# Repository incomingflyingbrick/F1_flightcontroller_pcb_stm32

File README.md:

# F1_flightcontroller_pcb_stm32

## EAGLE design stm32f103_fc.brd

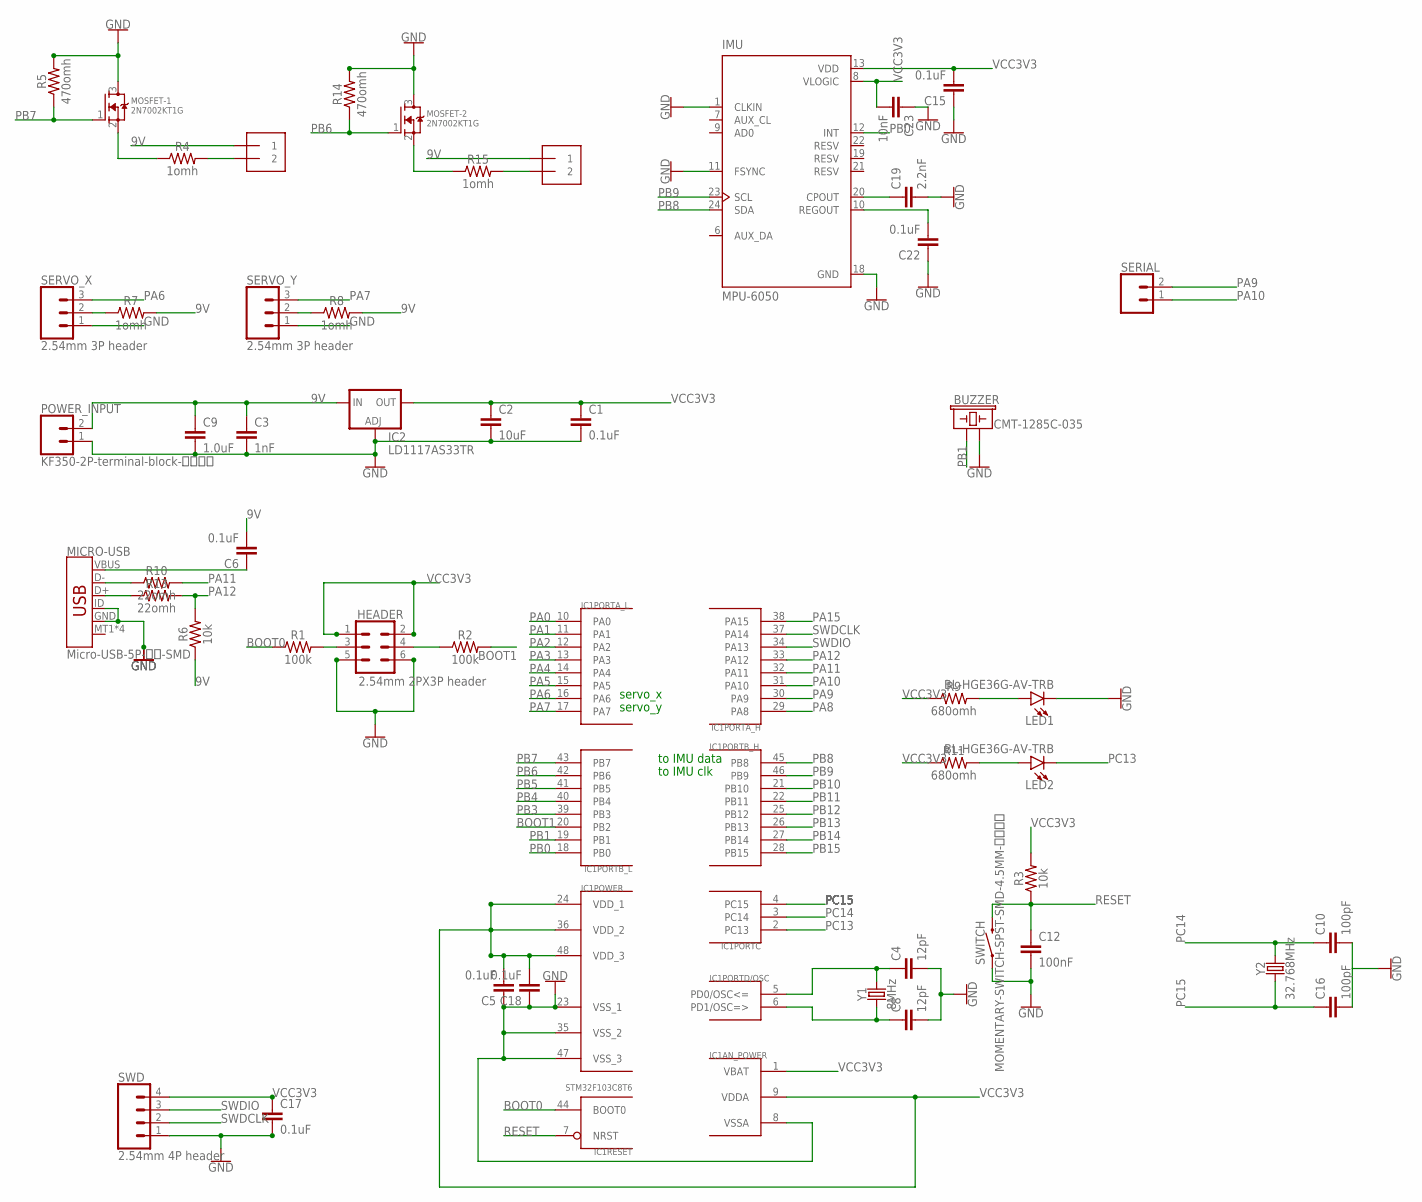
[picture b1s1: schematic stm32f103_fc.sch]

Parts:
BUZZER: CMT-1285C-035; BUZZER-12MM
C1, C6, C17: 0.1uF; 0603
C2: 10uF; 0603
C3: 1nF; 0603
C4, C8: 12pF; 0603
C5, C15, C18, C22: 0.1uF; 0402
C9: 1.0uF; 0603
C10, C16: 100pF; 0603
C12: 100nF; 0603
C19: 2.2nF; 0603
C23: 10nF; 0603
HEADER: 2.54mm 2PX3P header; 2X3-NS
IC1: STM32F103C8T6; TQFP48
IC2: LD1117AS33TR; SOT223
IMU: MPU-6050; QFN50P400X400X95-24N
LED1, LED2: BL-HGE36G-AV-TRB; LED-0603
MICRO-USB: Micro-USB-5P-无柱-SMD; USB-MICROB
MOSFET-1, MOSFET-2: 2N7002KT1G; SOT23
POWER_INPUT: KF350-2P-terminal-block-接线端子; SCREWTERMINAL-3.5MM-2
PY1, PY2: 1X2-3.5MM KF350 terminal block; 1X2-3.5MM
R1, R2: 100k; 0603
R3, R6: 10k; 0603
R4, R7, R8, R15: 1omh; 0603
R5, R14: 470omh; 0603
R9, R11: 680omh; 0603
R10, R13: 22omh; 0603
SERIAL: CONN_02; 1X02
SERVO_X: 2.54mm 3P header; 1X03
SERVO_Y: 2.54mm 3P header; 1X03
SWD: 2.54mm 4P header; 1X04
SWITCH: MOMENTARY-SWITCH-SPST-SMD-4.5MM-轻触开关; TACTILE_SWITCH_SMD_6.0X3.5MM
Y1: 8MHz; HC49US
Y2: 32.768MHz; HC49US

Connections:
9V: C3.1, C6.2, C9.1, IC2.3 (IN), POWER_INPUT.2, PY1.1, PY2.1, R6.1, R7.2, R8.2
BOOT0: IC1.44 (BOOT0), R1.1
BOOT1: IC1.20 (PB2), R2.2
GND: BUZZER.- (2), C1.2, C2.2, C3.2, C4.2, C5.1, C8.2, C9.2, C10.2, C12.2, C15.1, C16.2, C17.2, C18.1, C19.2, C22.1, C23.1, HEADER.5, HEADER.6, IC1.8 (VSSA), IC1.23 (VSS_1), IC1.35 (VSS_2), IC1.47 (VSS_3), IC2.1 (ADJ), IMU.1 (CLKIN), IMU.11 (FSYNC), IMU.18 (GND), LED1.C, MICRO-USB.GND, MICRO-USB.ID, MOSFET-1.3 (D), MOSFET-2.3 (D), POWER_INPUT.1, R5.2, R14.2, SERVO_X.1, SERVO_Y.1, SWD.1, SWITCH.1
unnamed: HEADER.3, R1.2
unnamed: HEADER.4, R2.1
unnamed: LED1.A, R9.2
unnamed: C19.1, IMU.20 (CPOUT)
unnamed: LED2.A, R11.2
unnamed: MICRO-USB.D-, R10.1
unnamed: C4.1, IC1.5 (PD0/OSC<=), Y1.2
unnamed: MICRO-USB.D+, R13.1
unnamed: C8.1, IC1.6 (PD1/OSC=>), Y1.1
unnamed: C6.1, MICRO-USB.VBUS
unnamed: PY1.2, R4.2
unnamed: PY2.2, R15.2
unnamed: MOSFET-2.2 (S), R15.1
unnamed: MOSFET-1.2 (S), R4.1
unnamed: C22.2, IMU.10 (REGOUT)
unnamed: R7.1, SERVO_X.2
unnamed: R8.1, SERVO_Y.2
PA0: IC1.10 (PA0)
PA1: IC1.11 (PA1)
PA2: IC1.12 (PA2)
PA3: IC1.13 (PA3)
PA4: IC1.14 (PA4)
PA5: IC1.15 (PA5)
PA6: IC1.16 (PA6), SERVO_X.3
PA7: IC1.17 (PA7), SERVO_Y.3
PA8: IC1.29 (PA8)
PA9: IC1.30 (PA9), SERIAL.2
PA10: IC1.31 (PA10), SERIAL.1
PA11: IC1.32 (PA11), R10.2
PA12: IC1.33 (PA12), R6.2, R13.2
PA15: IC1.38 (PA15)
PB0: IC1.18 (PB0), IMU.12 (INT)
PB1: BUZZER.+ (1), IC1.19 (PB1)
PB3: IC1.39 (PB3)
PB4: IC1.40 (PB4)
PB5: IC1.41 (PB5)
PB6: IC1.42 (PB6), MOSFET-2.1 (G), R14.1
PB7: IC1.43 (PB7), MOSFET-1.1 (G), R5.1
PB8: IC1.45 (PB8), IMU.24 (SDA)
PB9: IC1.46 (PB9), IMU.23 (SCL)
PB10: IC1.21 (PB10)
PB11: IC1.22 (PB11)
PB12: IC1.25 (PB12)
PB13: IC1.26 (PB13)
PB14: IC1.27 (PB14)
PB15: IC1.28 (PB15)
PC13: IC1.2 (PC13), LED2.C
PC14: C10.1, IC1.3 (PC14), Y2.2
PC15: C16.1, IC1.4 (PC15), Y2.1
RESET: C12.1, IC1.7 (NRST), R3.1, SWITCH.2
SWDCLK: IC1.37 (PA14), SWD.2
SWDIO: IC1.34 (PA13), SWD.3
VCC3V3: C1.1, C2.1, C5.2, C15.2, C17.1, C18.2, C23.2, HEADER.1, HEADER.2, IC1.1 (VBAT), IC1.9 (VDDA), IC1.24 (VDD_1), IC1.36 (VDD_2), IC1.48 (VDD_3), IC2.4 (OUT), IMU.8 (VLOGIC), IMU.13 (VDD), R3.2, R9.1, R11.1, SWD.4

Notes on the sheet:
to IMU data
to IMU clk
servo_x
servo_y

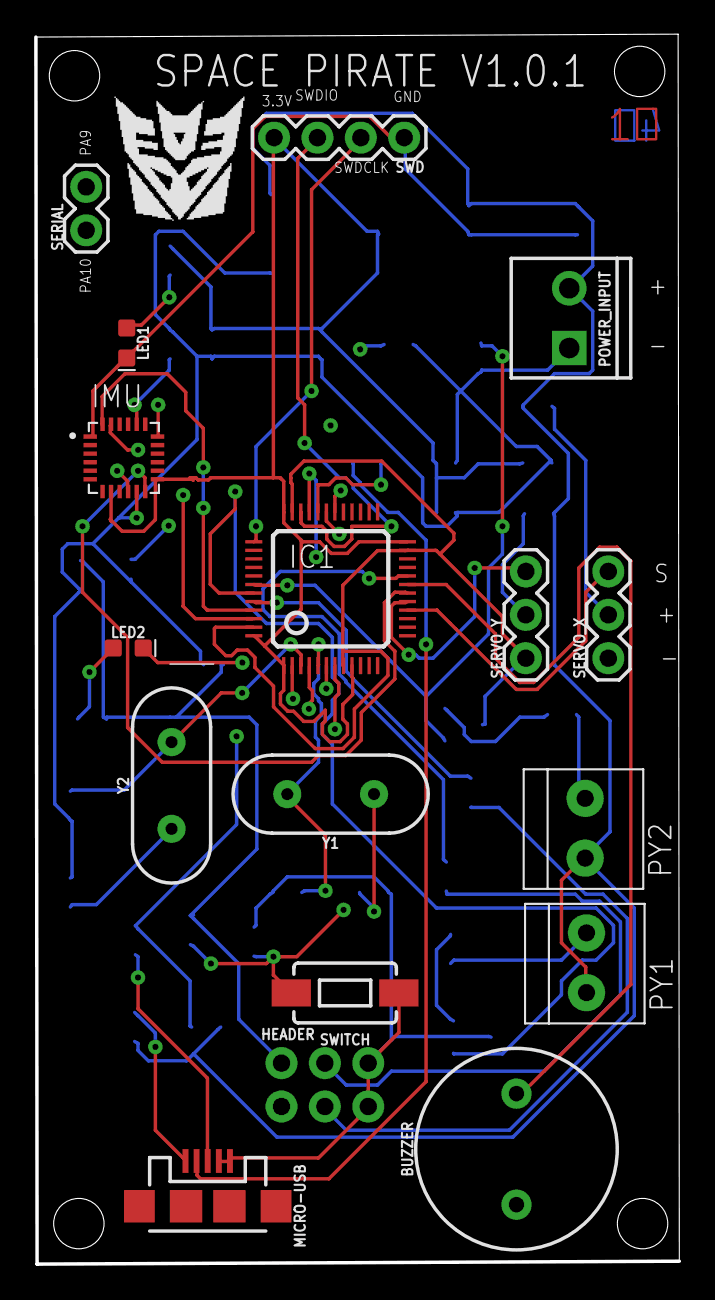
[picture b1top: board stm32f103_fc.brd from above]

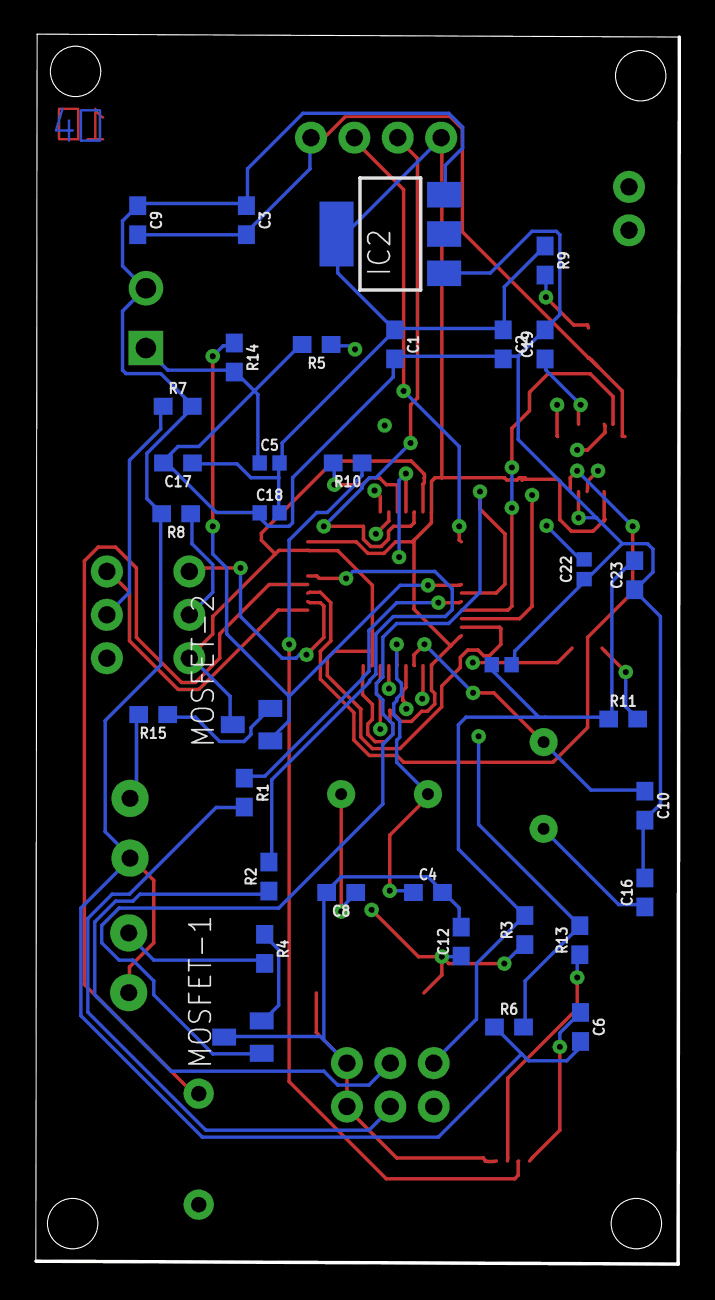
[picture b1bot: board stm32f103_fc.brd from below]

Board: 4 copper layers, 37.7 x 72.0 mm, 51 parts (34 on the bottom side), 40 nets.

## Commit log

2019-01-28 added more files
2019-01-29 added more lable
2019-01-31 added mpu-9250
2019-01-31 done some auto routing
2019-02-11 backup
2019-02-11 fixed board routing
2019-02-14 slim pcb
2019-02-15 added servo controller
2019-02-15 added version 1.0
2019-02-18 BOM next
2019-02-19 relayout board
2019-02-21 done
2019-02-21 done version 2
2019-02-21 done version 2 and cam
2019-02-23 done final cam
2019-02-24 change all width to 8mil
2019-03-01 added logo
2019-03-01 done with backside logo
2019-03-03 version 2.0
2019-03-03 version 2.0 done
2019-03-03 version 1.0.1 done
2019-03-03 version 1.0.1 done icon
2019-03-06 version 1.0.1 done fix transistor
2019-03-07 four layer board done
2019-03-07 four layer board done and generated gerber file
2019-03-07 fixed mirror issue
2019-03-20 added new switch
2019-04-07 added serial port

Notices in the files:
parts and their libraries:
SparkFun-Capacitors: Licensing: Creative Commons ShareAlike 4.0 International - https://creativecommons.org/licenses/by-sa/4.0
